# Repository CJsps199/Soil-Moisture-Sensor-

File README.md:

# Soil-Moisture-Sensor-
Soil Moisture sensor utilizing MCCI LMIC Library for LoRaWan© &amp; Chirpstack Network Server

# FOR SINGLE CHANNEL GATEWAY ONLY
Gateway & Sensor Node code.
Tweaked for my requirements.
# No Frequency Hopping.
# CAUTION
# NON "REGULATORY"
# USE AT OWN RISK
# Change each node's TX interval to best avoid conflict in receival on Gateway side

# Utilization of the great ChirpStack Network Server.
https://github.com/brocaar/chirpstack-network-server. (Thanks to Brocaar for this).

Using ESP8266 or ESP12F for the Gateway
Using Atmega 328P

See Eagle Drawings for compact Design of Sensor Node. +- 7cm x 4cm x 2cm.
Including MPPT Solar Charger CHIP. 
LiPo Battery Charger & Protection Circuit.

Gateway Drawing to come...

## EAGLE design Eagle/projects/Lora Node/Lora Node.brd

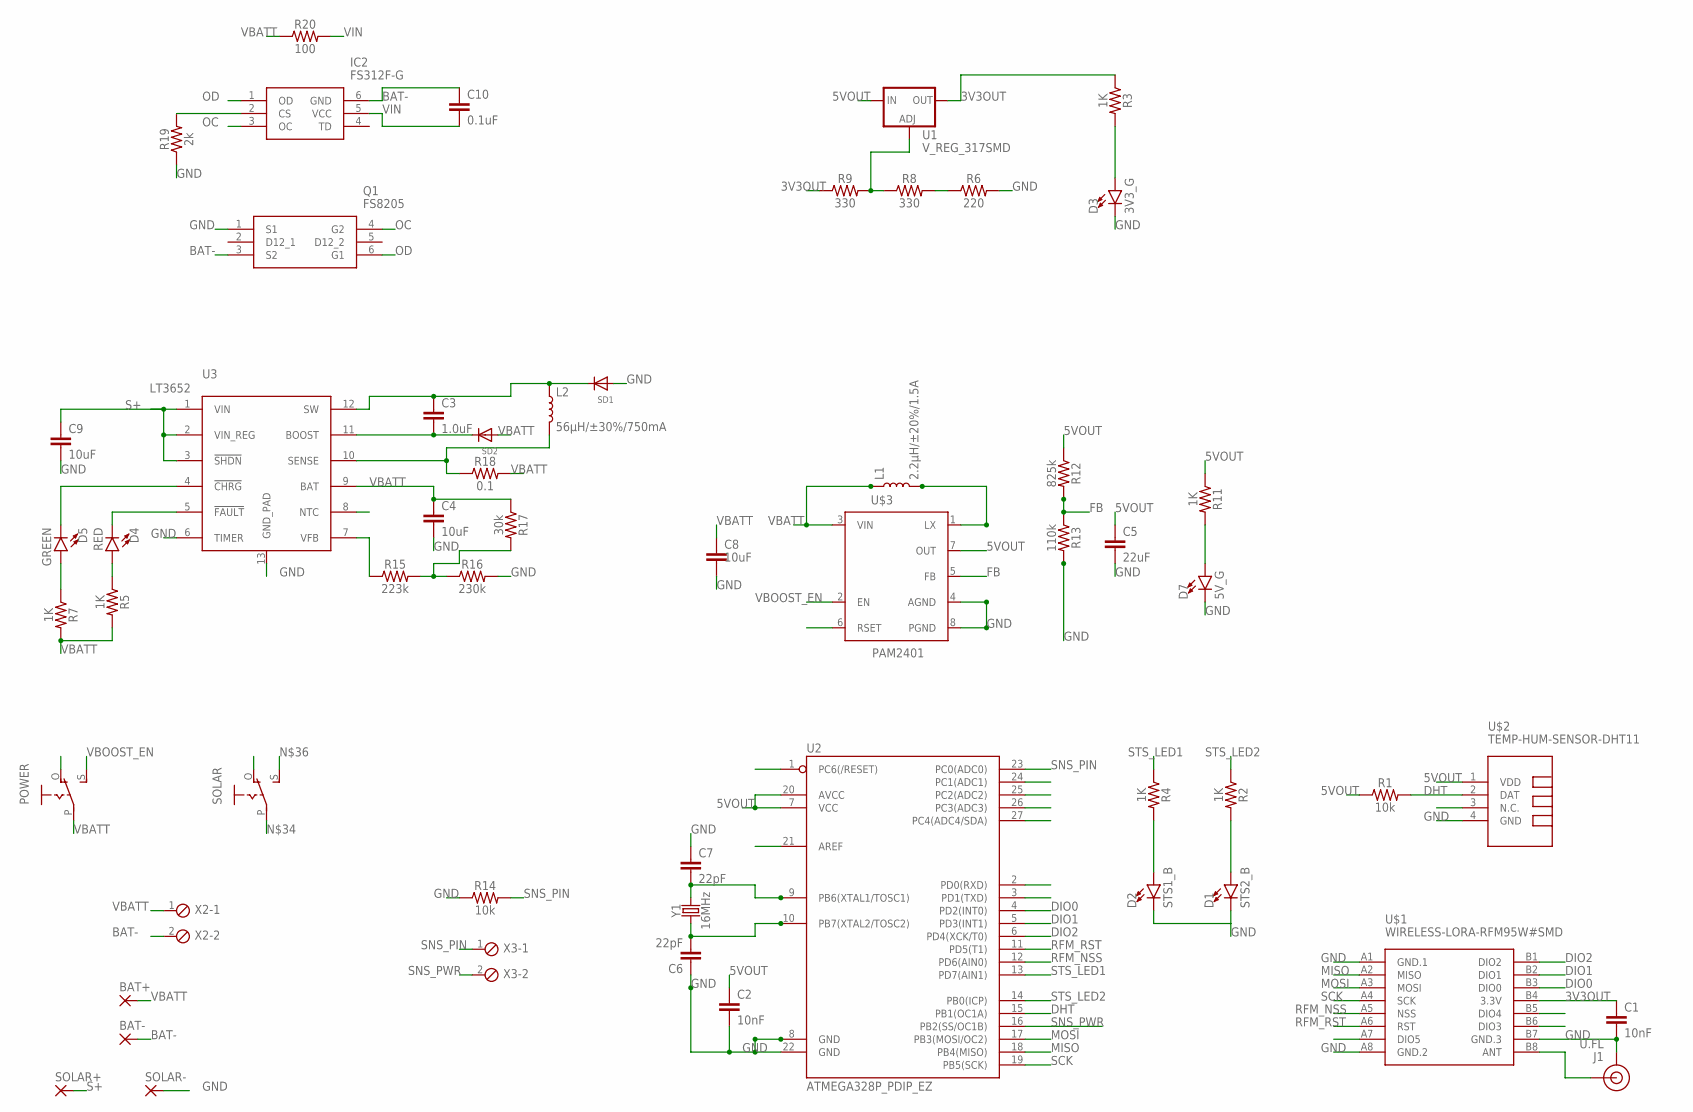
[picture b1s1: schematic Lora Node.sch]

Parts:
BAT+: SMD5; SMD2,54-5,08
BAT-: SMD5; SMD2,54-5,08
C1, C2: 10nF; 0603
C3: 1.0uF; 0805
C4, C8: 10uF; 0805
C5: 22uF; 0805
C6, C7: 22pF; 0603
C9: 10uF; 1210
C10: 0.1uF; 0603
D1: STS2_B; LED-1206
D2: STS1_B; LED-1206
D3: 3V3_G; LED-0603
D4: RED; LED-0603
D5: GREEN; LED-0603
D7: 5V_G; LED-0603
IC2: FS312F-G; SOT95P280X145-6N
J1: U.FL
L1: 2.2µH/±20%/1.5A; INDUCTOR_2.2UH
L2: 56µH/±30%/750mA; CR54
POWER: EG1218S; EG1218
Q1: FS8205
R1, R14: 10k; 0603
R2, R3, R4, R5, R7, R11: 1K; 0603
R6: 220; 0603
R8, R9: 330; 0603
R12: 825k; 0603
R13: 110k; 0603
R15: 223k; 0603
R16: 230k; 0603
R17: 30k; 0603
R18: 0.1; 1210
R19: 2k; 0603
R20: 100; 0603
SD1, SD2: DIODESMA; SMADIODE
SOLAR: EG1218S; EG1218
SOLAR+: SMD5; SMD2,54-5,08
SOLAR-: SMD5; SMD2,54-5,08
U1: V_REG_317SMD; SOT223
U2: ATMEGA328P_PDIP_EZ; DIP28-SIMON-KIT
U3: LT3652; MSOP-12_GND
U$1: WIRELESS-LORA-RFM95W#SMD
U$2: TEMP-HUM-SENSOR-DHT11
U$3: PAM2401; MSOP8
X2, X3: MPT2; 2POL254
Y1: 16MHz; HC49US

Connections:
3V3OUT: C1.1, R3.1, R9.1, U1.2 (OUT), U$1.B4 (3.3V)
5VOUT: C2.1, C5.1, R1.1, R11.1, R12.1, U1.3 (IN), U2.7 (VCC), U2.20 (AVCC), U$2.1 (VDD), U$3.7 (OUT)
BAT-: BAT-.1, C10.1, IC2.6 (GND), Q1.3 (S2), X2.2
DHT: R1.2, U2.15 (PB1(OC1A)), U$2.2 (DAT)
DIO0: U2.4 (PD2(INT0)), U$1.B3 (DIO0)
DIO1: U2.5 (PD3(INT1)), U$1.B2 (DIO1)
DIO2: U2.6 (PD4(XCK/T0)), U$1.B1 (DIO2)
FB: R12.2, R13.1, U$3.5 (FB)
GND: C1.2, C2.2, C4.2, C5.2, C6.1, C7.1, C8.2, C9.2, D1.C, D2.C, D3.C, D7.C, J1.1 (GND), J1.2 (GND), Q1.1 (S1), R6.2, R13.2, R14.1, R16.2, R19.1, SD1.A, SOLAR-.1, U2.8 (GND), U2.22 (GND), U3.6 (TIMER), U3.13 (GND_PAD), U$1.A1 (GND.1), U$1.A8 (GND.2), U$1.B7 (GND.3), U$2.4 (GND), U$3.4 (AGND), U$3.8 (PGND)
MISO: U2.18 (PB4(MISO)), U$1.A2 (MISO)
MOSI: U2.17 (PB3(MOSI/OC2)), U$1.A3 (MOSI)
unnamed: C7.2, U2.9 (PB6(XTAL1/TOSC1)), Y1.2
unnamed: C6.2, U2.10 (PB7(XTAL2/TOSC2)), Y1.1
unnamed: D7.A, R11.2
unnamed: D5.A, R7.1
unnamed: D3.A, R3.2
unnamed: D2.A, R4.2
unnamed: D1.A, R2.2
unnamed: D4.A, R5.1
unnamed: D5.C, U3.4 (!CHRG)
unnamed: D4.C, U3.5 (!FAULT)
unnamed: C3.1, L2.P$1 (1), SD1.C, U3.12 (SW)
unnamed: C3.2, SD2.C, U3.11 (BOOST)
unnamed: IC2.2 (CS), R19.2
unnamed: L2.P$2 (2), R18.1, U3.10 (SENSE)
unnamed: R15.1, U3.7 (VFB)
unnamed: R15.2, R16.1, R17.2
unnamed: J1.FEED (SIGNAL), U$1.B8 (ANT)
unnamed: R6.1, R8.2
unnamed: L1.P$2 (2), U$3.1 (LX)
unnamed: R8.1, R9.2, U1.1 (ADJ)
OC: IC2.3 (OC), Q1.4 (G2)
OD: IC2.1 (OD), Q1.6 (G1)
RFM_NSS: U2.12 (PD6(AIN0)), U$1.A5 (NSS)
RFM_RST: U2.11 (PD5(T1)), U$1.A6 (RST)
S+: C9.1, SOLAR+.1, U3.1 (VIN), U3.2 (VIN_REG), U3.3 (!SHDN)
SCK: U2.19 (PB5(SCK)), U$1.A4 (SCK)
SNS_PIN: R14.2, U2.23 (PC0(ADC0)), X3.1
SNS_PWR: U2.16 (PB2(SS/OC1B)), X3.2
STS_LED1: R4.1, U2.13 (PD7(AIN1))
STS_LED2: R2.1, U2.14 (PB0(ICP))
VBATT: BAT+.1, C4.1, C8.1, L1.P$1 (1), POWER.P, R5.2, R7.2, R17.1, R18.2, R20.1, SD2.A, U3.9 (BAT), U$3.3 (VIN), X2.1
VBOOST_EN: POWER.S, U$3.2 (EN)
VIN: C10.2, IC2.5 (VCC), R20.2

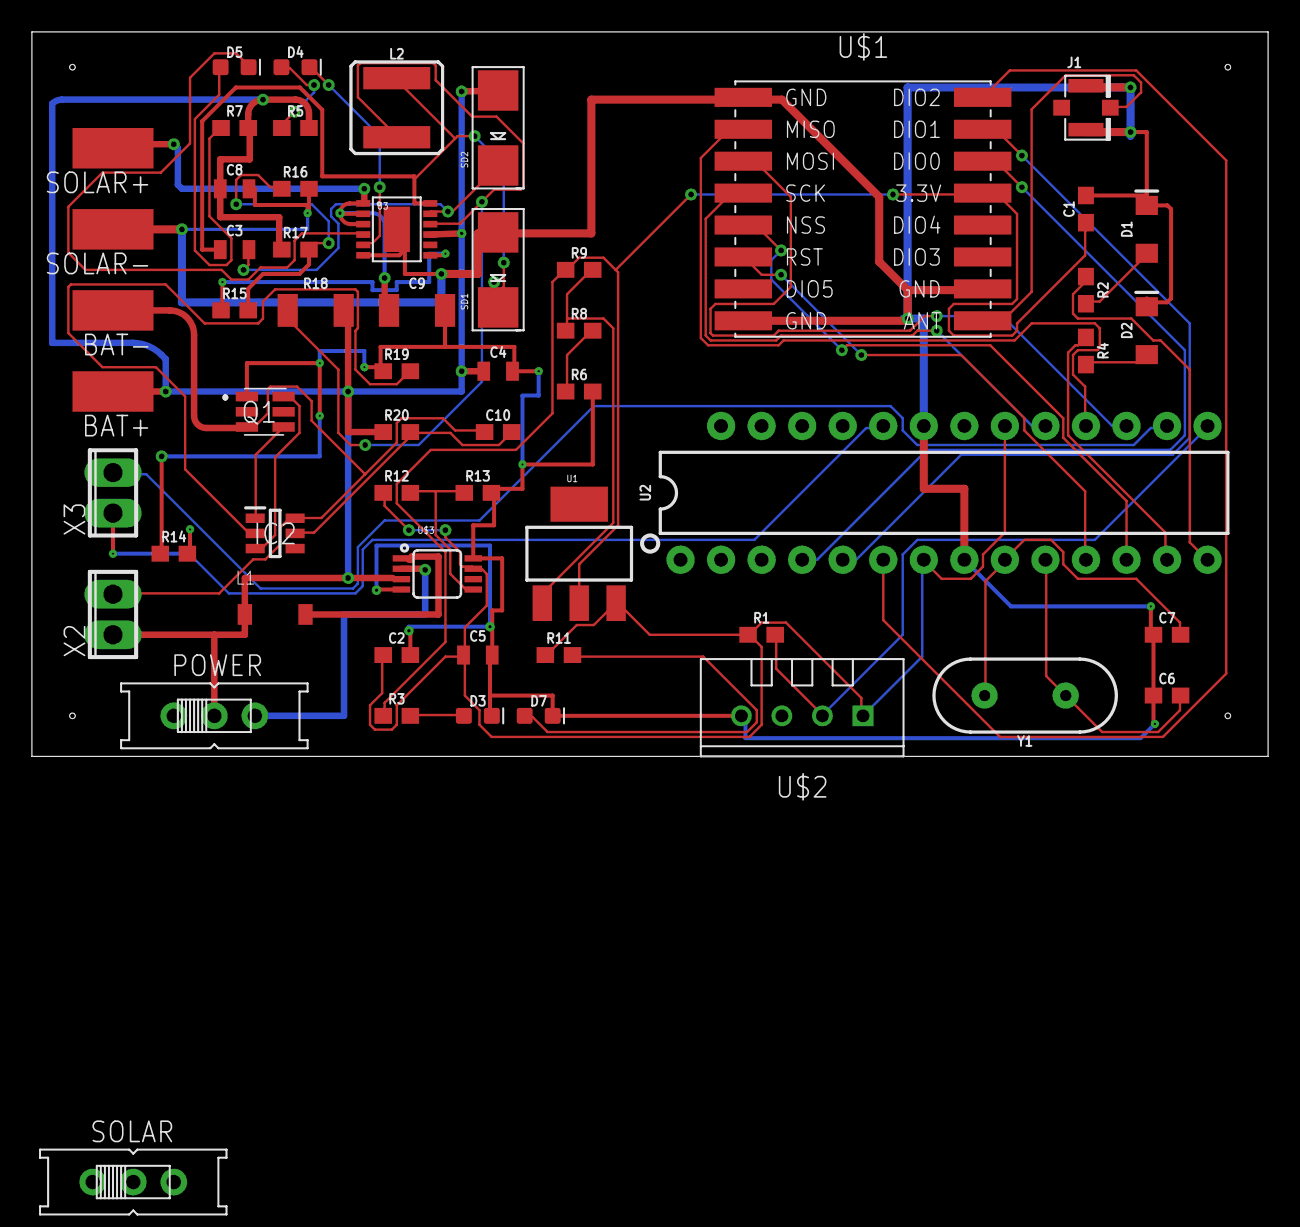
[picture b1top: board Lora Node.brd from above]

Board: 2 copper layers, 77.5 x 45.4 mm, 57 parts (0 on the bottom side), 44 nets.

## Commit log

2021-09-17 Added Correct MCCI Library
2021-09-17 Eagle Drawings

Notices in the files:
parts and their libraries:
diy-modules: Released under the Creative Commons Attribution 4.0 International License: http://creativecommons.org/licenses/by/4.0
SparkFun-Clocks: Licensing: Creative Commons ShareAlike 4.0 International - https://creativecommons.org/licenses/by-sa/4.0
